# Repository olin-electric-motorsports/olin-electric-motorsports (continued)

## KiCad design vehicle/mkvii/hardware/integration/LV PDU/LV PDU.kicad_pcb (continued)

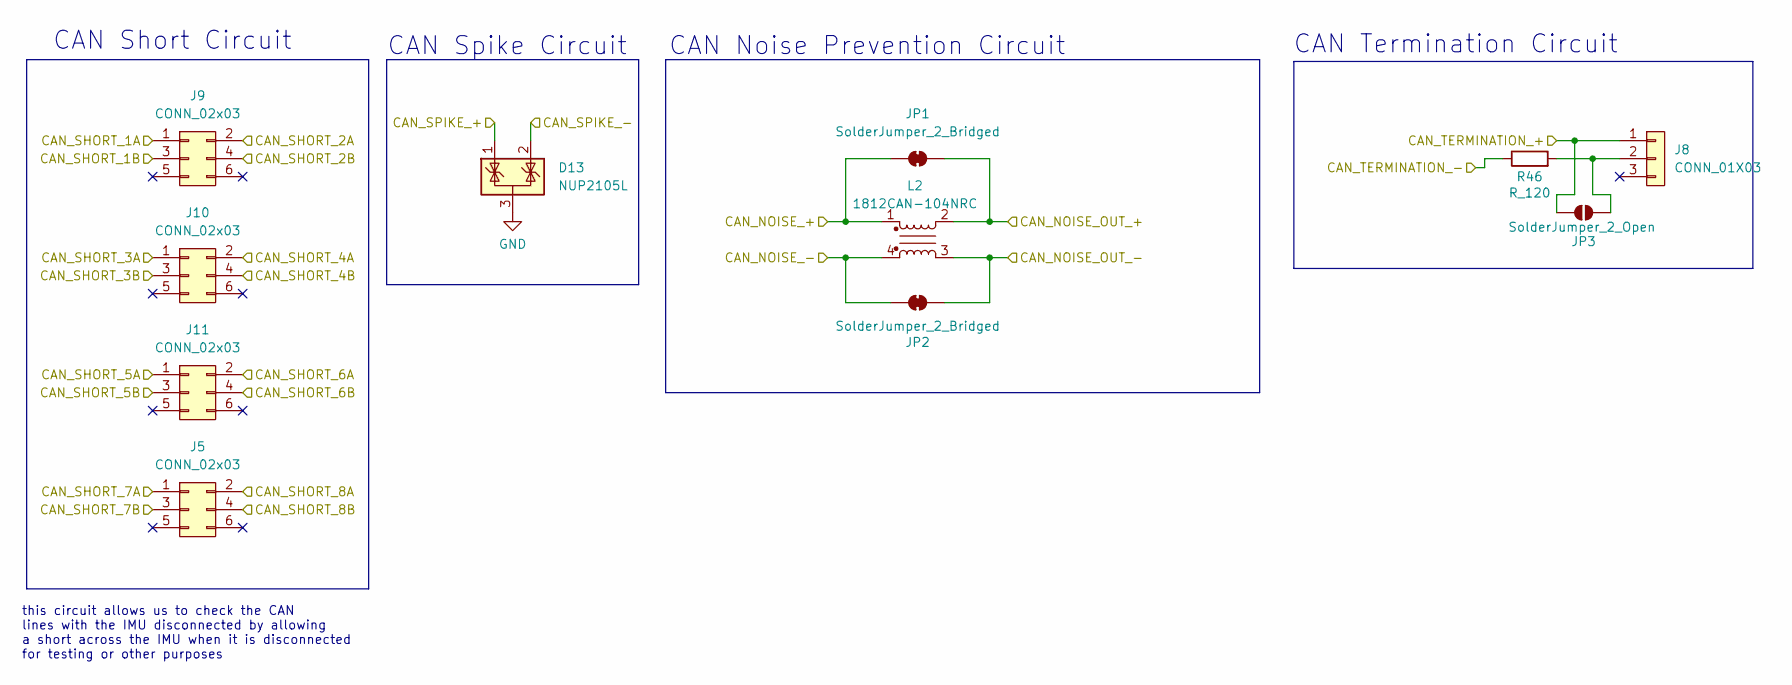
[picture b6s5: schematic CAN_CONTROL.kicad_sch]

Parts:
D13: NUP2105L; SOT-23
J5, J9, J10, J11: CONN_02x03; PinHeader_2x03_P2.54mm_Vertical; MPN 10129381-906002BLF
J8: CONN_01X03; PinHeader_1x03_P2.54mm_Vertical; MPN PH1-03-UA
JP1, JP2: SolderJumper_2_Bridged; SolderJumper-2_P1.3mm_Bridged2Bar_Pad1.0x1.5mm
JP3: SolderJumper_2_Open; SolderJumper-2_P1.3mm_Open_Pad1.0x1.5mm
L2: 1812CAN-104NRC; L_CommonModeChoke_Coilcraft_1812CAN
R46: R_120; R_0603; MPN RC0603FR-13120RL

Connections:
/CAN_1+: J8.1, J9.1, JP3.2 (B); also elsewhere on the board
/CAN_1-: J9.2, R46.1; also elsewhere on the board
/CAN_2+: J9.3, J10.1; also elsewhere on the board
/CAN_2-: J9.4, J10.2; also elsewhere on the board
/CAN_3+: J10.3, J11.1; also elsewhere on the board
/CAN_3-: J10.4, J11.2; also elsewhere on the board
/CAN_4+: J5.4, J11.3; also elsewhere on the board
/CAN_4-: J5.3, J11.4; also elsewhere on the board
/CAN_5+: D13.1 (K), J5.1, JP1.2 (B), L2.2; also elsewhere on the board
/CAN_5-: D13.2 (K), J5.2, JP2.1 (A), L2.3; also elsewhere on the board
/CAN_6+: JP2.2 (B), L2.4; also elsewhere on the board
/CAN_6-: JP1.1 (A), L2.1; also elsewhere on the board
GND: D13.3 (A); also elsewhere on the board
unnamed: J8.2, JP3.1 (A), R46.2

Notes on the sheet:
CAN Short Circuit
CAN Noise Prevention Circuit
this circuit allows us to check the CAN lines with the IMU disconnected by allowing a short across the IMU when it is disconnected for testing or other purposes
CAN Spike Circuit
CAN Termination Circuit

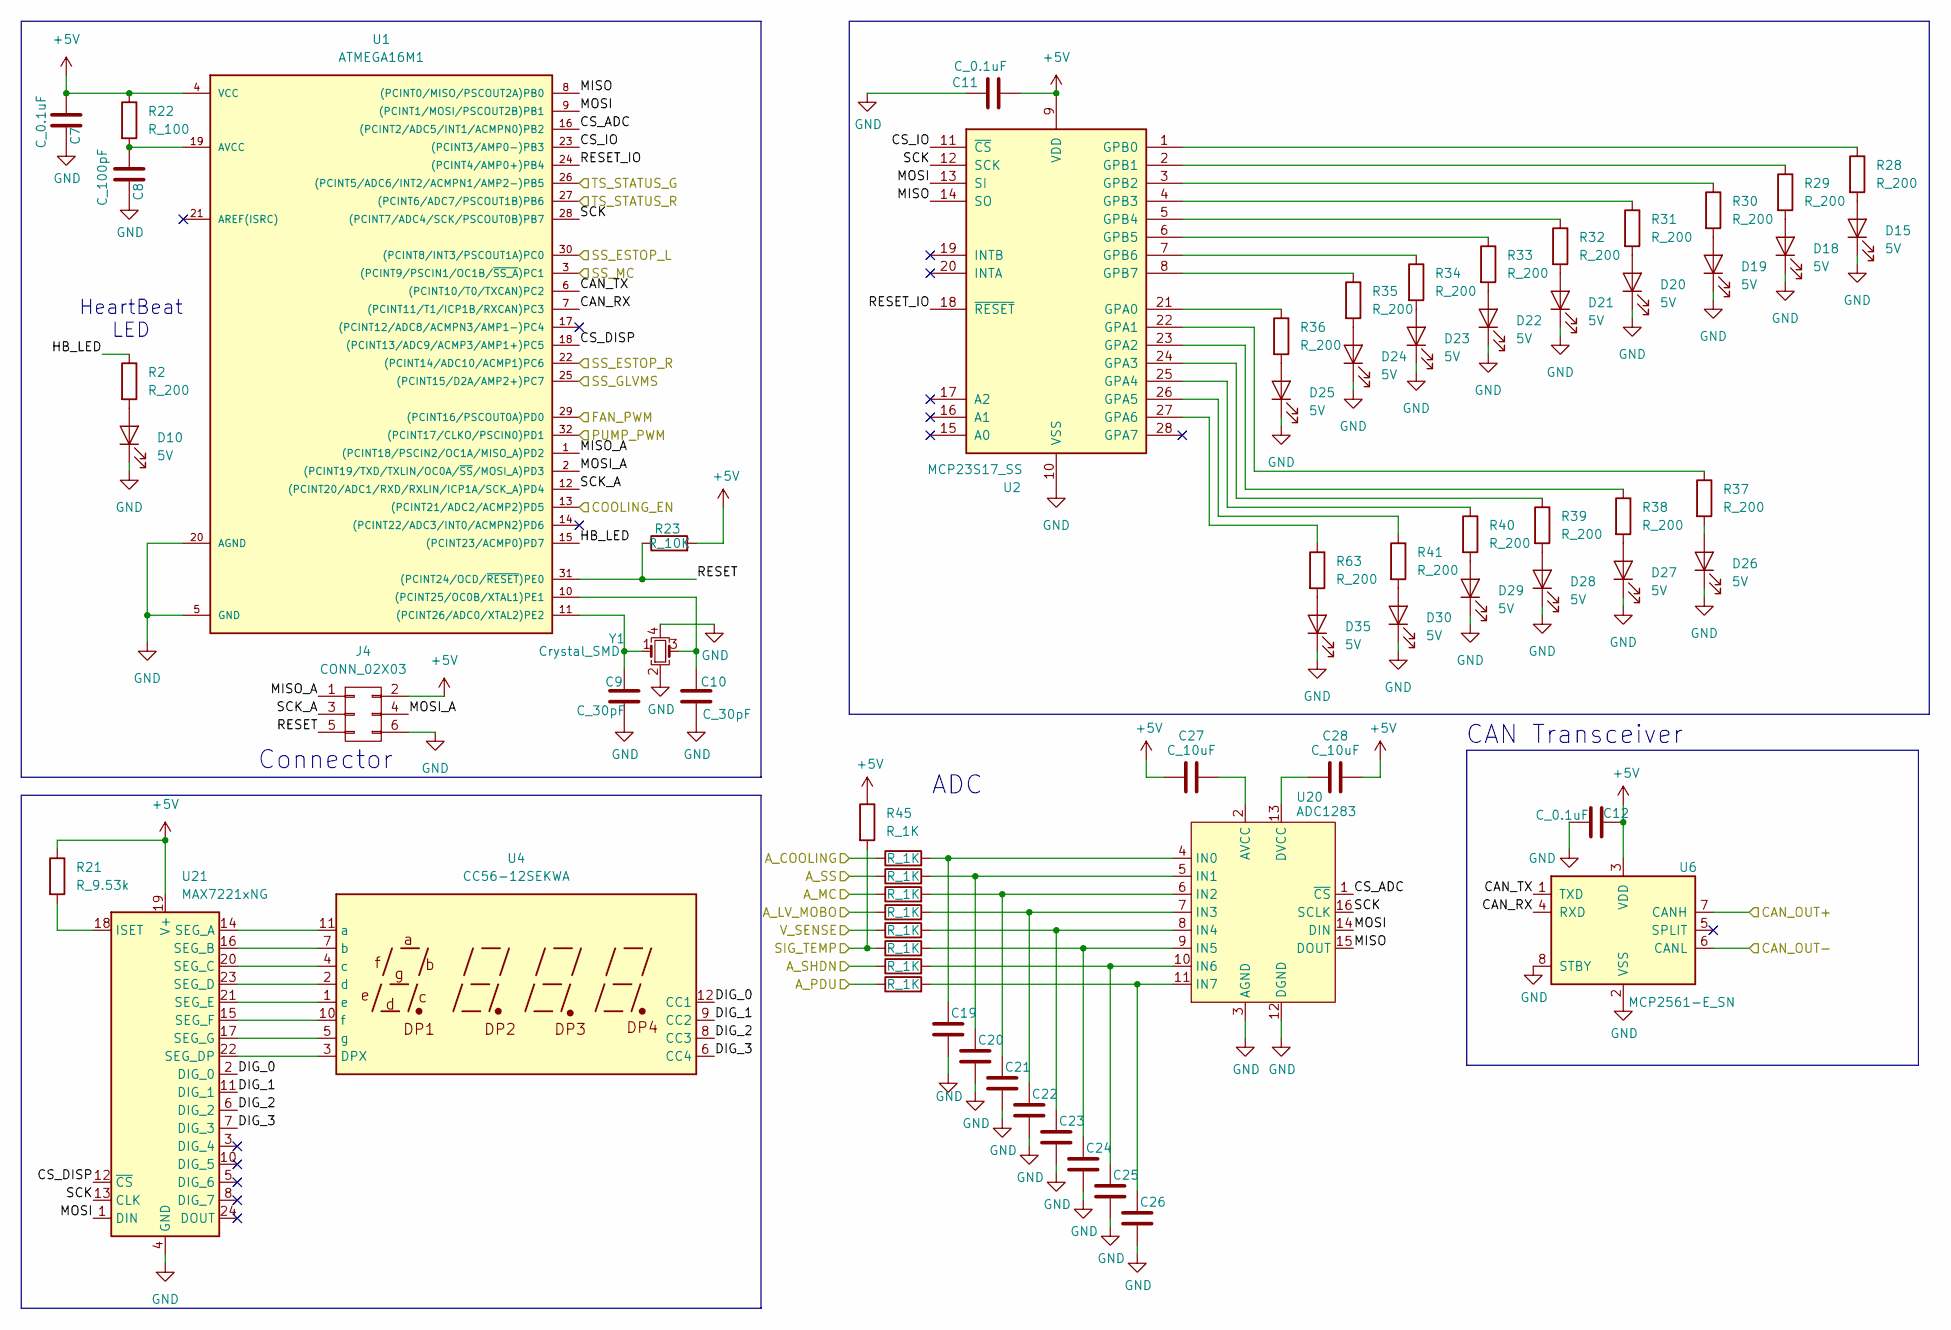
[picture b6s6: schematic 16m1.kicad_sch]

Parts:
C7, C11, C12: C_0.1uF; C_0603_1608Metric; MPN 478-3352-1-ND
C8: C_100pF; C_0603_1608Metric; MPN 732-7852-1-ND
C9, C10: C_30pF; C_0603_1608Metric; MPN 1276-1130-1-ND
C19, C20, C21, C22, C23, C24, C25, C26, C27, C28: C_10uF; C_0603; MPN LMK107BBJ106KALT
D10, D15, D18, D19, D20, D21, D22, D23, D24, D25, D26, D27, D28, D29, D30, D35: 5V; CHIPLED_0805; MPN 475-1410-1-ND
J4: CONN_02X03; PinHeader_2x03_P2.54mm_Vertical; MPN 609-3234-ND
R2, R28, R29, R30, R31, R32, R33, R34, R35, R36, R37, R38, R39, R40, R41, R63: R_200; R_0603; MPN RC0603FR-13200RL
R11, R20, R45, R54, R55, R56, R57, R58, R59: R_1K; R_0603; MPN RMCF0603FT1K00
R21: R_9.53k; R_0603; MPN RMCF0603FT1K91
R22: R_100; R_0603; MPN RMCF0603FT100R
R23: R_10K; R_0603; MPN RMCF0603FT10K0
U1: ATMEGA16M1; TQFP-32_7x7mm_Pitch0.8mm; MPN ATMEGA16M1-AU-ND
U2: MCP23S17_SS; SSOP-28_5.3x10.2mm_P0.65mm
U4: CC56-12SEKWA; CA56-12SEKWA
U6: MCP2561-E_SN; SOIC-8_3.9x4.9mm_Pitch1.27mm_OEM; MPN MCP2561-E/SN-ND
U20: ADC1283; TSSOP-16_4.4x5mm_P0.65mm
U21: MAX7221xNG; DIP-24_W7.62mm
Y1: Crystal_SMD; Crystal_SMD_FA238; MPN 887-1125-1-ND

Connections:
+5V: C7.1, C11.2, C12.1, C27.1, C28.2, J4.2, R21.1, R22.1, R23.2, R45.1, U1.4 (VCC), U2.9 (VDD), U6.3 (VDD), U21.19 (V+); also elsewhere on the board
/AS_COOL: R11.1; also elsewhere on the board
/AS_LV: R55.1; also elsewhere on the board
/AS_MC: R54.1; also elsewhere on the board
/AS_PDU: R59.1; also elsewhere on the board
/AS_SHDN: R58.1; also elsewhere on the board
/AS_SS: R20.1; also elsewhere on the board
/CAN_1+: U6.7 (CANH); also elsewhere on the board
/CAN_1-: U6.6 (CANL); also elsewhere on the board
/COOLING_EN: U1.13 ((PCINT21/ADC2/ACMP2)PD5); also elsewhere on the board
/FAN_PWM: U1.29 ((PCINT16/PSCOUT0A)PD0); also elsewhere on the board
/Microcontroller/CAN_RX: U1.7 ((PCINT11/T1/ICP1B/RXCAN)PC3), U6.4 (RXD)
/Microcontroller/CAN_TX: U1.6 ((PCINT10/T0/TXCAN)PC2), U6.1 (TXD)
/Microcontroller/CS_ADC: U1.16 ((PCINT2/ADC5/INT1/ACMPN0)PB2), U20.1 (~CS)
/Microcontroller/CS_DISP: U1.18 ((PCINT13/ADC9/ACMP3/AMP1+)PC5), U21.12 (~CS)
/Microcontroller/CS_IO: U1.23 ((PCINT3/AMP0-)PB3), U2.11 (~CS)
/Microcontroller/DIG_0: U4.12 (CC1), U21.2 (DIG_0)
/Microcontroller/DIG_1: U4.9 (CC2), U21.11 (DIG_1)
/Microcontroller/DIG_2: U4.8 (CC3), U21.6 (DIG_2)
/Microcontroller/DIG_3: U4.6 (CC4), U21.7 (DIG_3)
/Microcontroller/HB_LED: R2.1, U1.15 ((PCINT23/ACMP0)PD7)
/Microcontroller/MISO: U1.8 ((PCINT0/MISO/PSCOUT2A)PB0), U2.14 (SO), U20.15 (DOUT)
/Microcontroller/MISO_A: J4.1, U1.1 ((PCINT18/PSCIN2/OC1A/MISO_A)PD2)
/Microcontroller/MOSI: U1.9 ((PCINT1/MOSI/PSCOUT2B)PB1), U2.13 (SI), U20.14 (DIN), U21.1 (DIN)
/Microcontroller/MOSI_A: J4.4, U1.2 ((PCINT19/TXD/TXLIN/OC0A/~SS/MOSI_A)PD3)
/Microcontroller/RESET: J4.5, R23.1, U1.31 ((PCINT24/OCD/~RESET)PE0)
/Microcontroller/RESET_IO: U1.24 ((PCINT4/AMP0+)PB4), U2.18 (~RESET)
/Microcontroller/SCK: U1.28 ((PCINT7/ADC4/SCK/PSCOUT0B)PB7), U2.12 (SCK), U20.16 (SCLK), U21.13 (CLK)
/Microcontroller/SCK_A: J4.3, U1.12 ((PCINT20/ADC1/RXD/RXLIN/ICP1A/SCK_A)PD4)
/PUMP_PWM: U1.32 ((PCINT17/CLKO/PSCIN0)PD1); also elsewhere on the board
/SIG_TEMP: R45.2, R57.1; also elsewhere on the board
/SS_ESTOP_L: U1.30 ((PCINT8/INT3/PSCOUT1A)PC0); also elsewhere on the board
/SS_ESTOP_R: U1.22 ((PCINT14/ADC10/ACMP1)PC6); also elsewhere on the board
/SS_GLVMS: U1.25 ((PCINT15/D2A/AMP2+)PC7); also elsewhere on the board
/SS_MC: U1.3 ((PCINT9/PSCIN1/OC1B/~SS_A)PC1); also elsewhere on the board
/TS_STAT_G: U1.26 ((PCINT5/ADC6/INT2/ACMPN1/AMP2-)PB5); also elsewhere on the board
/TS_STAT_R: U1.27 ((PCINT6/ADC7/PSCOUT1B)PB6); also elsewhere on the board
/V_SENSE: R56.1; also elsewhere on the board
GND: C7.2, C8.2, C9.2, C10.2, C11.1, C12.2, C19.2, C20.2, C21.2, C22.2, C23.2, C24.2, C25.2, C26.2, D10.1 (K), D15.1 (K), D18.1 (K), D19.1 (K), D20.1 (K), D21.1 (K), D22.1 (K), D23.1 (K), D24.1 (K), D25.1 (K), D26.1 (K), D27.1 (K), D28.1 (K), D29.1 (K), D30.1 (K), D35.1 (K), J4.6, U1.5 (GND), U1.20 (AGND), U2.10 (VSS), U6.2 (VSS), U6.8 (STBY), U20.3 (AGND), U20.12 (DGND), U21.4 (GND), U21.9 (GND), Y1.2, Y1.4; also elsewhere on the board
unnamed: D10.2 (A), R2.2
unnamed: D15.2 (A), R28.2
unnamed: D18.2 (A), R29.2
unnamed: D19.2 (A), R30.2
unnamed: D20.2 (A), R31.2
unnamed: D21.2 (A), R32.2
unnamed: D22.2 (A), R33.2
unnamed: D23.2 (A), R34.2
unnamed: D24.2 (A), R35.2
unnamed: D25.2 (A), R36.2
unnamed: D26.2 (A), R37.2
unnamed: D27.2 (A), R38.2
unnamed: D28.2 (A), R39.2
unnamed: D29.2 (A), R40.2
unnamed: D30.2 (A), R41.2
unnamed: D35.2 (A), R63.2
unnamed: C10.1, U1.10 ((PCINT25/OC0B/XTAL1)PE1), Y1.3
unnamed: C9.1, U1.11 ((PCINT26/ADC0/XTAL2)PE2), Y1.1
unnamed: C8.1, R22.2, U1.19 (AVCC)
unnamed: R36.1, U2.21 (GPA0)
unnamed: R37.1, U2.22 (GPA1)
unnamed: R38.1, U2.23 (GPA2)
unnamed: R39.1, U2.24 (GPA3)
unnamed: R40.1, U2.25 (GPA4)
unnamed: R41.1, U2.26 (GPA5)
unnamed: R63.1, U2.27 (GPA6)
unnamed: R28.1, U2.1 (GPB0)
unnamed: R29.1, U2.2 (GPB1)
unnamed: R30.1, U2.3 (GPB2)
unnamed: R31.1, U2.4 (GPB3)
unnamed: R32.1, U2.5 (GPB4)
unnamed: R33.1, U2.6 (GPB5)
unnamed: R34.1, U2.7 (GPB6)
unnamed: R35.1, U2.8 (GPB7)
unnamed: C27.2, U20.2 (AVCC)
unnamed: C28.1, U20.13 (DVCC)
unnamed: C19.1, R11.2, U20.4 (IN0)
unnamed: C20.1, R20.2, U20.5 (IN1)
unnamed: C21.1, R54.2, U20.6 (IN2)
unnamed: C22.1, R55.2, U20.7 (IN3)
unnamed: C23.1, R56.2, U20.8 (IN4)
unnamed: C24.1, R57.2, U20.9 (IN5)
unnamed: C25.1, R58.2, U20.10 (IN6)
unnamed: C26.1, R59.2, U20.11 (IN7)
unnamed: R21.2, U21.18 (ISET)
unnamed: U4.11 (a), U21.14 (SEG_A)
unnamed: U4.7 (b), U21.16 (SEG_B)
unnamed: U4.4 (c), U21.20 (SEG_C)
unnamed: U4.2 (d), U21.23 (SEG_D)
unnamed: U4.3 (DPX), U21.22 (SEG_DP)
unnamed: U4.1 (e), U21.21 (SEG_E)
unnamed: U4.10 (f), U21.15 (SEG_F)
unnamed: U4.5 (g), U21.17 (SEG_G)

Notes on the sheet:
HeartBeat LED
ADC
Connector
CAN Transceiver

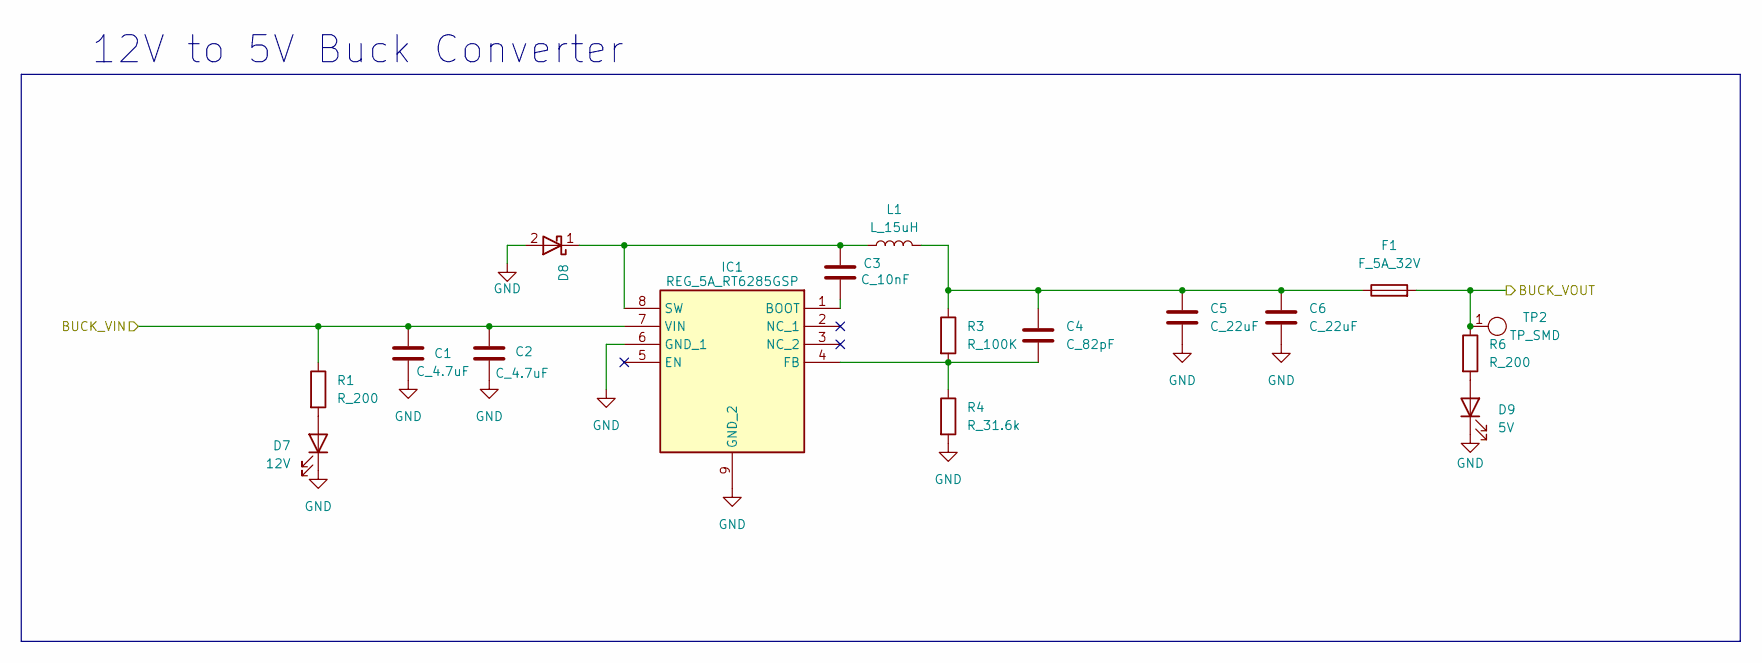
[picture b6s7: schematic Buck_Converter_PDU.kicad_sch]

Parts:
C1, C2: C_4.7uF; C_0603; MPN GRT188R61E475ME13D
C3: C_10nF; C_0603; MPN CL10B103KB8NNNC
C4: C_82pF; C_0603
C5, C6: C_22uF; C_1206_3216Metric; MPN CL31A226KAHNNNE
D7: 12V; CHIPLED_0805; MPN B1701TW--20P000314U1930
D8: D_Schottky_B550C-13-F; SMC_DIO-M; MPN D_B550C-13-F
D9: 5V; CHIPLED_0805; MPN B1701TW--20P000314U1930
F1: F_5A_32V; Fuse_1206; MPN FHC32502ADTP
IC1: REG_5A_RT6285GSP; SOIC127P600X175-9N; Mouser Part Number 835-RT6285GSP
L1: L_15uH; NR10050T150M; MPN NR10050T150M
R1, R6: R_200; R_0603; MPN RC0603FR-13200RL
R3: R_100K; R_0603; MPN RMCF0603FT100K
R4: R_31.6k; R_0603; MPN RMCF0603FT75K0
TP2: TP_SMD; Test_Point_SMD; MPN 5019

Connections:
+5V: F1.2, R6.1, TP2.1; also elsewhere on the board
/12V_PDU: C1.1, C2.1, IC1.7 (VIN), R1.1; also elsewhere on the board
GND: C1.2, C2.2, C5.2, C6.2, D7.1 (K), D8.2 (A), D9.1 (K), IC1.6 (GND_1), IC1.9 (GND_2), R4.2; also elsewhere on the board
unnamed: C4.1, C5.1, C6.1, F1.1, L1.2, R3.1
unnamed: D7.2 (A), R1.2
unnamed: C3.1, D8.1 (K), IC1.8 (SW), L1.1
unnamed: D9.2 (A), R6.2
unnamed: C3.2, IC1.1 (BOOT)
unnamed: C4.2, IC1.4 (FB), R3.2, R4.1

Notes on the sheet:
12V to 5V Buck Converter

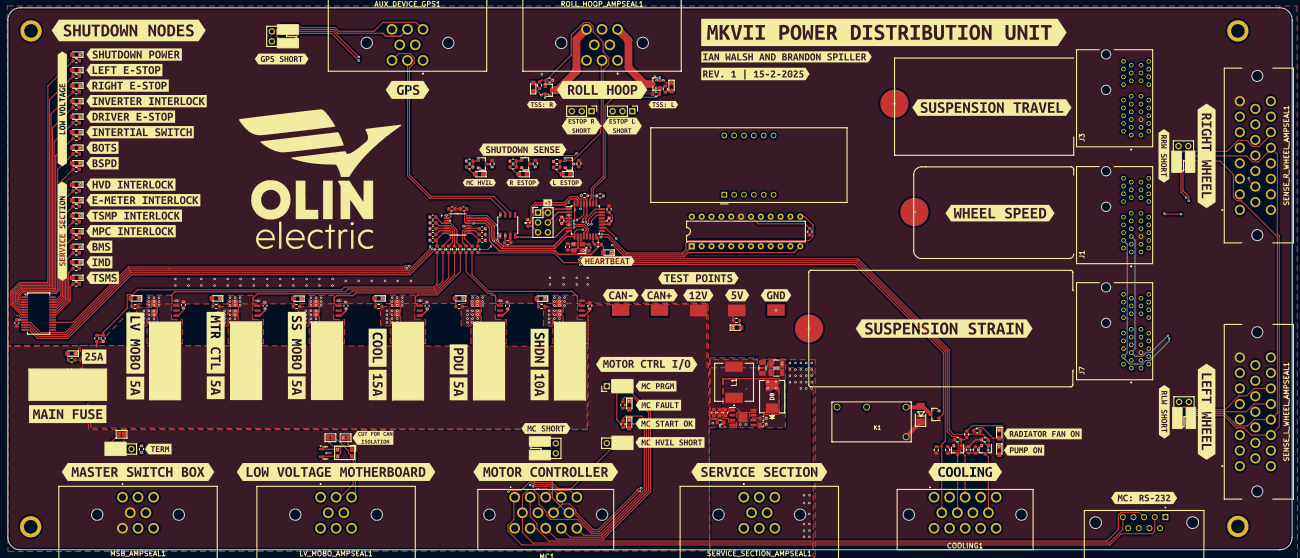
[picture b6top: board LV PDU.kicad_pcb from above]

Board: 4 copper layers, 330.7 x 139.5 mm, 270 parts (0 on the bottom side), 167 nets.

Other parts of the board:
kibuzzard-67AB0958: G***; kibuzzard-67AB0958
kibuzzard-67ABF04C: G***; kibuzzard-67ABF04C
kibuzzard-67ABF8F6: G***; kibuzzard-67ABF8F6
kibuzzard-67ABF070: G***; kibuzzard-67ABF070
kibuzzard-67ABFB32, kibuzzard-67ABFB32#2, kibuzzard-67ABFB32#3, kibuzzard-67ABFB32#4: G***; kibuzzard-67ABFB32
kibuzzard-67ABFB75: G***; kibuzzard-67ABFB75
kibuzzard-67ABFF94: G***; kibuzzard-67ABFF94
kibuzzard-67AC01C8: G***; kibuzzard-67AC01C8
kibuzzard-67AC003F: G***; kibuzzard-67AC003F
kibuzzard-67AC0064: G***; kibuzzard-67AC0064
kibuzzard-67AC128F: G***; kibuzzard-67AC128F
kibuzzard-67AC0345: G***; kibuzzard-67AC0345
kibuzzard-67AC0354: G***; kibuzzard-67AC0354
kibuzzard-67AD82A4: G***; kibuzzard-67AD82A4
kibuzzard-67AD82AC: G***; kibuzzard-67AD82AC
kibuzzard-67AD92CF: G***; kibuzzard-67AD92CF
kibuzzard-67AD9297: G***; kibuzzard-67AD9297
kibuzzard-67ADA3CD: G***; kibuzzard-67ADA3CD
kibuzzard-67ADA8C1: G***; kibuzzard-67ADA8C1
kibuzzard-67ADA9AA: G***; kibuzzard-67ADA9AA
kibuzzard-67ADA9CC: G***; kibuzzard-67ADA9CC
kibuzzard-67ADA9D8: G***; kibuzzard-67ADA9D8
kibuzzard-67ADA9DE: G***; kibuzzard-67ADA9DE
kibuzzard-67ADA42A: G***; kibuzzard-67ADA42A
kibuzzard-67ADA91A: G***; kibuzzard-67ADA91A
kibuzzard-67ADA98D: G***; kibuzzard-67ADA98D
kibuzzard-67ADA440: G***; kibuzzard-67ADA440
kibuzzard-67ADA446: G***; kibuzzard-67ADA446
kibuzzard-67ADA961: G***; kibuzzard-67ADA961
kibuzzard-67ADA969: G***; kibuzzard-67ADA969
kibuzzard-67ADA976: G***; kibuzzard-67ADA976
kibuzzard-67ADA981: G***; kibuzzard-67ADA981
kibuzzard-67ADA997: G***; kibuzzard-67ADA997
kibuzzard-67ADAA00: G***; kibuzzard-67ADAA00
kibuzzard-67ADB137: G***; kibuzzard-67ADB137
kibuzzard-67ADB153: G***; kibuzzard-67ADB153
kibuzzard-67ADB212: G***; kibuzzard-67ADB212
kibuzzard-67ADB303: G***; kibuzzard-67ADB303
kibuzzard-67AEBB92: G***; kibuzzard-67AEBB92
kibuzzard-67AEBBB3: G***; kibuzzard-67AEBBB3
kibuzzard-67AED8CC: G***; kibuzzard-67AED8CC
kibuzzard-67AEE0BC: G***; kibuzzard-67AEE0BC
kibuzzard-67AEE0F7: G***; kibuzzard-67AEE0F7
kibuzzard-67AEE1ED: G***; kibuzzard-67AEE1ED
kibuzzard-67AEE3A0: G***; kibuzzard-67AEE3A0
kibuzzard-67AEE3B5: G***; kibuzzard-67AEE3B5
kibuzzard-67AEE3DB: G***; kibuzzard-67AEE3DB
kibuzzard-67AEE3F9: G***; kibuzzard-67AEE3F9
kibuzzard-67AEE6A3: G***; kibuzzard-67AEE6A3
kibuzzard-67AEE6B3: G***; kibuzzard-67AEE6B3
kibuzzard-67AEE6BC: G***; kibuzzard-67AEE6BC
kibuzzard-67AEE69C: G***; kibuzzard-67AEE69C
kibuzzard-67AEE386: G***; kibuzzard-67AEE386
kibuzzard-67AEE693: G***; kibuzzard-67AEE693
kibuzzard-67AEE978: G***; kibuzzard-67AEE978
kibuzzard-67AF6B32: G***; kibuzzard-67AF6B32
kibuzzard-67AF66A9: G***; kibuzzard-67AF66A9
kibuzzard-67AF6632: G***; kibuzzard-67AF6632
kibuzzard-67AF6652: G***; kibuzzard-67AF6652
kibuzzard-67AFAC6D: G***; kibuzzard-67AFAC6D
kibuzzard-67AFAC82: G***; kibuzzard-67AFAC82
kibuzzard-67AFB15F: G***; kibuzzard-67AFB15F
kibuzzard-67AFB48D: G***; kibuzzard-67AFB48D
kibuzzard-67AFB152: G***; kibuzzard-67AFB152
kibuzzard-67AFB489: G***; kibuzzard-67AFB489
kibuzzard-67B14BD7: G***; kibuzzard-67B14BD7
kibuzzard-67B14D77: G***; kibuzzard-67B14D77
kibuzzard-67B14D85: G***; kibuzzard-67B14D85
kibuzzard-67B152AE: G***; kibuzzard-67B152AE
kibuzzard-67B15964: G***; kibuzzard-67B15964
kibuzzard-675B44FA: G***; kibuzzard-675B44FA
kibuzzard-675B44FE: G***; kibuzzard-675B44FE
kibuzzard-675B459C: G***; kibuzzard-675B459C
kibuzzard-675B4597: G***; kibuzzard-675B4597

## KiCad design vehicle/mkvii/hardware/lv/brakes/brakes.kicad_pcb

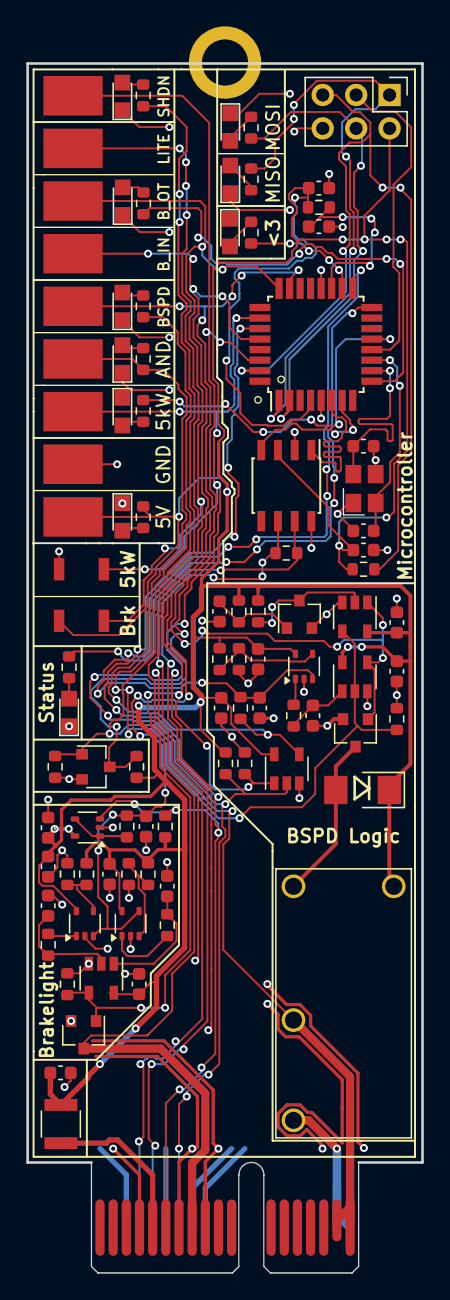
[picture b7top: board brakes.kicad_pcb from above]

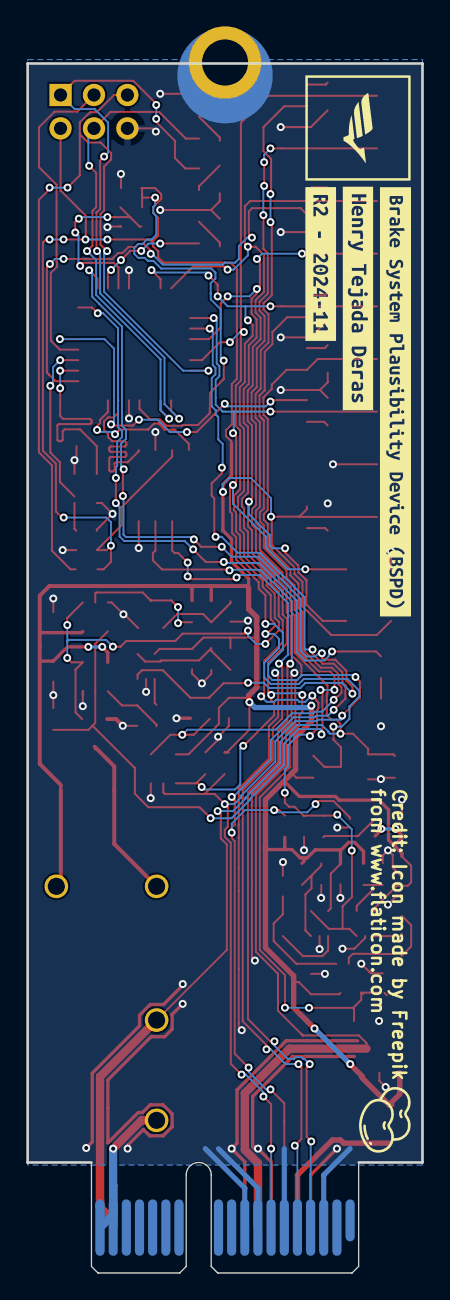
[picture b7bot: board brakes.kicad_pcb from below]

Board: 2 copper layers, 30.0 x 91.9 mm, 98 parts (3 on the bottom side), 53 nets.

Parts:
C1, C3, C4, C5, C8, C9, C10, C11, C13, C14, C20: C_0.1uF; C_0603
C2, C7, C15: C_1uF; C_0603
C6, C21: C_10uF; C_0603
C12: C_0.22uF; C_0603
C16: C_100pF; C_0603
C17, C18: C_30pF; C_0603
D1: BSPD_TRIP_LED; CHIPLED_0805
D2: HEARTBEAT; CHIPLED_0805
D3: BSPD_TRIP; CHIPLED_0805
D4: 5V_LED; CHIPLED_0805
D5: D_Zener_18V_SMBJ5355B-TP; DO-214AA
D6: BSPD_GATE_TRIP; CHIPLED_0805
D7: MISO_PROG_LED; CHIPLED_0805
D8: MOTOR ON; CHIPLED_0805
D9: Shutdown_LED; CHIPLED_0805
D10: BRAKES; CHIPLED_0805
D13: MOSI_PROG_LED; CHIPLED_0805
F1: F_500mA_16V; Fuse_1210
H1: CONN_MountingHole; PCIe_Mount
J1: CONN_pcie_x1; pcie_x1
J3: CONN_02x03; PinHeader_2x03_P2.54mm_Vertical
K2: Relay_G5Q-1A4-DC5; Relay_SPST_OMRON-G5Q-1A4_OEM
Q2, Q3, Q4, Q5: Q_NMOS_SSM3K333R; SOT-23F
R1: R_576; R_0603
R2, R4, R5, R6, R12, R14, R15, R17, R20, R23, R31, R35: R_10K; R_0603
R3, R22: R_100; R_0603
R7: R_120; R_0603
R8, R10, R16, R19, R24, R25, R26, R27, R30, R32: R_1K; R_0603
R9, R11, R18, R34: R_100K; R_0603
R13: R_71.5K; R_0603
R21: R_75K; R_0603
R33: R_3K; R_0603
SW1, SW2: SW_Push_SPST_NO; SW_B3U-1000P_4.2x1.7mm
TP1: B_OT; Test_Point_SMD
TP2: LITE; Test_Point_SMD
TP3: GND; Test_Point_SMD
TP4: BSPD; Test_Point_SMD
TP5: SHDN; Test_Point_SMD
TP7: 5kW; Test_Point_SMD
TP8: B_IN; Test_Point_SMD
TP10: AND; Test_Point_SMD
TP11: 5V; Test_Point_SMD
U1: U_CAN_MCP2561; SOIC-8_3.9x4.9mm_Pitch1.27mm_OEM
U2, U3, U4, U6: U_OPAMP_MCP6001; SOT-353_SC-70-5
U5, U7: U_GATE_SN74LVC1G02DBVR; SOT-23-5_OEM
U8: U_GATE_SN74LVC1G32DBVR; SOT-23-5_OEM
U9: U_GATE_SN74LVC1G08DBVR; SOT-23-5_OEM
U10: U_ATMEGA16M1; TQFP-32_7x7mm_Pitch0.8mm
Y1: X_Crystal_16MHz_18pF; Crystal_TXC7M
kibuzzard-672D5534: G***; kibuzzard-672D5534
kibuzzard-672D6696: G***; kibuzzard-672D6696
kibuzzard-673C20EC: G***; kibuzzard-673C20EC

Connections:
+5V: C1.1, C3.1, C4.1, C5.1, C6.1, C8.1, C9.1, C10.1, C13.1, C14.2, C20.1, D5.1 (K), F1.1, J3.2, K2.5, R1.1, R2.1, R11.1, R12.1, R15.2, R20.1, R22.1, R23.1, R26.2, R31.1, R34.1, SW2.1, TP11.1, U1.3 (VDD), U2.5 (V+), U3.5 (V+), U4.5 (V+), U5.5 (VCC), U6.5 (V+), U7.5 (VCC), U8.5 (VCC), U9.5 (VCC), U10.4 (VCC)
/BSPD/BRAKELIGHT_LL: Q5.1 (G), R6.2, R9.1, SW2.2, TP1.1, U8.4 (out), U9.1 (in), U10.24 ((PCINT4/AMP0+)PB4)
/BSPD/BSPD_LL: Q3.1 (G), TP4.1, U5.4 (out), U7.1 (in), U10.23 ((PCINT3/AMP0-)PB3)
/BSPD/BSPD_RELAY_IN: J1.A17 (SHDN_IN/io_22), J1.A18 (SHDN_IN/io_24), K2.3
/BSPD/BSPD_RELAY_OUT: J1.B17 (SHDN_OUT/io_23), J1.B18 (SHDN_OUT/io_25), K2.2, Q2.1 (G), R18.1, R33.2
/BSPD/MOTOR_CURRENT_SENSE: J1.A7 (io_2), R34.2, SW1.2, TP7.1, U9.2 (in), U10.26 ((PCINT5/ADC6/INT2/ACMPN1/AMP2-)PB5)
/BSPD/RC_TIMER_STATUS: C21.1, R13.1, U4.3 (+), U10.17 ((PCINT12/ADC8/ACMPN3/AMP1-)PC4)
/BrakeLight/BRAKELIGHT_CONN: J1.B8 (io_5), Q5.3 (D), TP2.1
/BrakeLight/BRAKE_PRESS_SENSE: J1.B6 (io_1), R2.2, U6.3 (+), U10.27 ((PCINT6/ADC7/PSCOUT1B)PB6)
/BrakeLight/BRAKE_PRESS_SENSE_FILTERED: C12.1, R21.2, TP8.1, U2.3 (+), U3.4 (-), U10.28 ((PCINT7/ADC4/SCK/PSCOUT0B)PB7)
/Microcontroller - ATMEGA16M1/5KW_LED: R8.2, U10.13 ((PCINT21/ADC2/ACMP2)PD5)
/Microcontroller - ATMEGA16M1/BRAKE_LL_LED: R19.2, U10.9 ((PCINT1/MOSI/PSCOUT2B)PB1)
/Microcontroller - ATMEGA16M1/BSPD_SHUTDOWN_SENSE: Q2.3 (D), R20.2, TP5.1, U10.30 ((PCINT8/INT3/PSCOUT1A)PC0)
/Microcontroller - ATMEGA16M1/BSPD_TRIP_LED: R16.2, U10.16 ((PCINT2/ADC5/INT1/ACMPN0)PB2)
/Microcontroller - ATMEGA16M1/CAN_+: J1.A4 (CAN+), R7.1, U1.7 (CANH)
/Microcontroller - ATMEGA16M1/CAN_-: J1.A5 (CAN-), R7.2, U1.6 (CANL)
/Microcontroller - ATMEGA16M1/CAN_RX: U1.4 (RXD), U10.7 ((PCINT11/T1/ICP1B/RXCAN)PC3)
/Microcontroller - ATMEGA16M1/CAN_TX: U1.1 (TXD), U10.6 ((PCINT10/T0/TXCAN)PC2)
/Microcontroller - ATMEGA16M1/HEARTBEAT_LED: R24.1, U10.18 ((PCINT13/ADC9/ACMP3/AMP1+)PC5)
/Microcontroller - ATMEGA16M1/MISO: J3.1, R27.2, U10.1 ((PCINT18/PSCIN2/OC1A/MISO_A)PD2)
/Microcontroller - ATMEGA16M1/MOSI: J3.4, R32.2, U10.2 ((PCINT19/TXD/TXLIN/OC0A/~SS/MOSI_A)PD3)
/Microcontroller - ATMEGA16M1/RESET: J3.5, R23.2, U10.31 ((PCINT24/OCD/~RESET)PE0)
/Microcontroller - ATMEGA16M1/SCK: J3.3, U10.12 ((PCINT20/ADC1/RXD/RXLIN/ICP1A/SCK_A)PD4)
GND: C1.2, C2.2, C3.2, C4.2, C5.2, C6.2, C7.2, C8.2, C9.2, C10.2, C11.1, C12.2, C13.2, C14.1, C15.2, C16.2, C17.2, C18.2, C20.2, C21.2, D1.1 (K), D2.1 (K), D3.1 (K), D4.1 (K), D6.1 (K), D7.1 (K), D8.1 (K), D9.1 (K), D10.1 (K), D13.1 (K), H1.1, J1.A3 (GND), J1.A6 (io_0), J1.A8 (io_4), J1.A9 (io_6), J1.B4 (GND), J1.B7 (io_3), J1.B9 (io_7), J3.6, Q2.2 (S), Q3.2 (S), Q4.2 (S), Q5.2 (S), R3.2, R6.1, R9.2, R14.2, R17.2, R18.2, R30.2, SW1.1, TP3.1, U1.2 (VSS), U1.8 (STBY), U2.2 (V-), U3.2 (V-), U4.2 (V-), U5.3 (GND), U6.2 (V-), U7.3 (GND), U8.3 (GND), U9.3 (GND), U10.5 (GND), U10.20 (AGND), Y1.2, Y1.4
unnamed: C2.1, R5.1, U8.2 (in)
unnamed: C7.1, R35.2, U5.1 (in)
unnamed: C15.1, R4.1, U8.1 (in)
unnamed: D1.2 (A), R25.2
unnamed: D2.2 (A), R24.2
unnamed: D3.2 (A), R16.1
unnamed: D4.2 (A), R26.1
unnamed: D5.2 (A), K2.1, Q3.3 (D)
unnamed: D6.2 (A), R10.2
unnamed: D7.2 (A), R27.1
unnamed: D8.2 (A), R8.1
unnamed: D9.2 (A), R33.1
unnamed: D10.2 (A), R19.1
unnamed: D13.2 (A), R32.1
unnamed: F1.2, J1.B5 (5V)
unnamed: Q4.3 (D), R11.2, U7.2 (in)
unnamed: C11.2, Q4.1 (G), R15.1
unnamed: R4.2, U3.1
unnamed: R5.2, U2.1
unnamed: R35.1, U4.1
unnamed: R1.2, R3.1, U2.4 (-)
unnamed: R30.1, R31.2, U3.3 (+)
unnamed: R12.2, R14.1, U4.4 (-)
unnamed: R21.1, U6.1, U6.4 (-)
unnamed: R17.1, R25.1, U5.2 (in), U7.4 (out)
unnamed: R10.1, R13.2, TP10.1, U9.4 (out)
unnamed: C18.1, U10.10 ((PCINT25/OC0B/XTAL1)PE1), Y1.3
unnamed: C17.1, U10.11 ((PCINT26/ADC0/XTAL2)PE2), Y1.1
unnamed: C16.1, R22.2, U10.19 (AVCC)
